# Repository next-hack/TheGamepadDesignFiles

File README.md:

# TheGamepadDesignFiles
 KiCAD design files for The Gamepad, an open source handheld console based on the Arduino Nano Matter Board.

**Notes**
Please use KiCAD 8.0 or later.
Each item in the schematics has its own part number filled so you can easily create the bill of materials.

Building: see https://next-hack.com/index.php/2024/09/21/the-gamepad-an-open-source-diy-handheld-gaming-console

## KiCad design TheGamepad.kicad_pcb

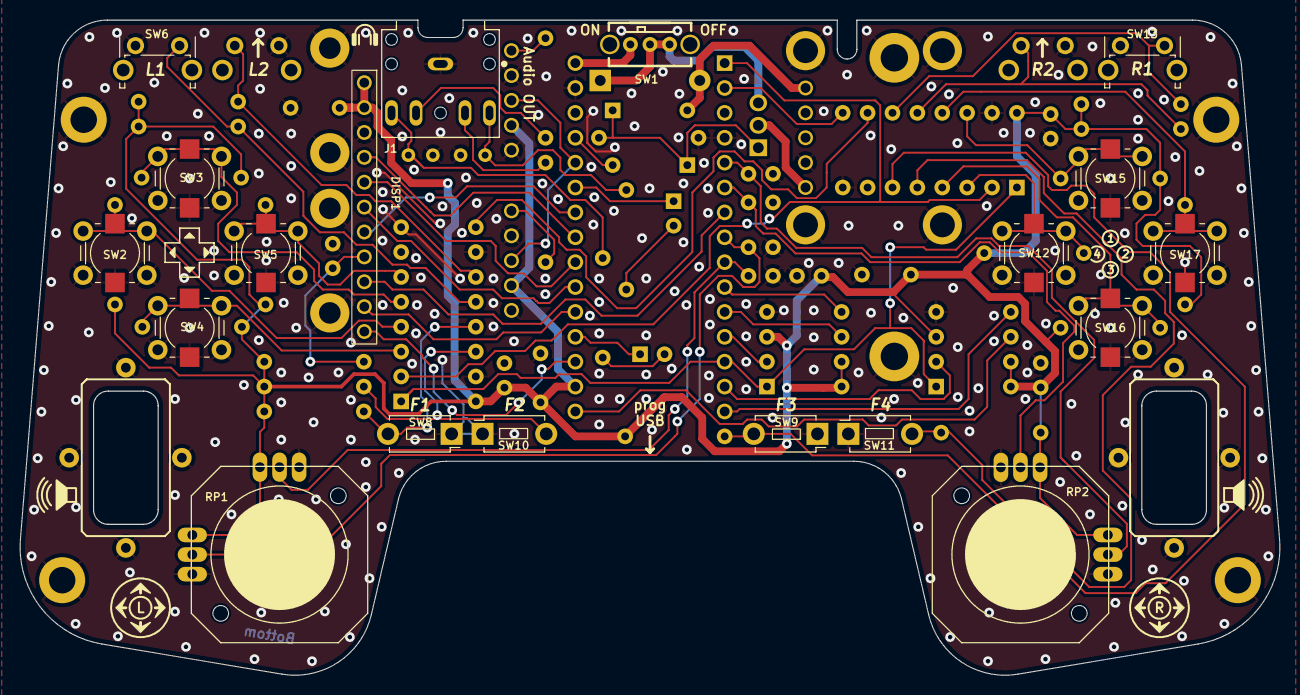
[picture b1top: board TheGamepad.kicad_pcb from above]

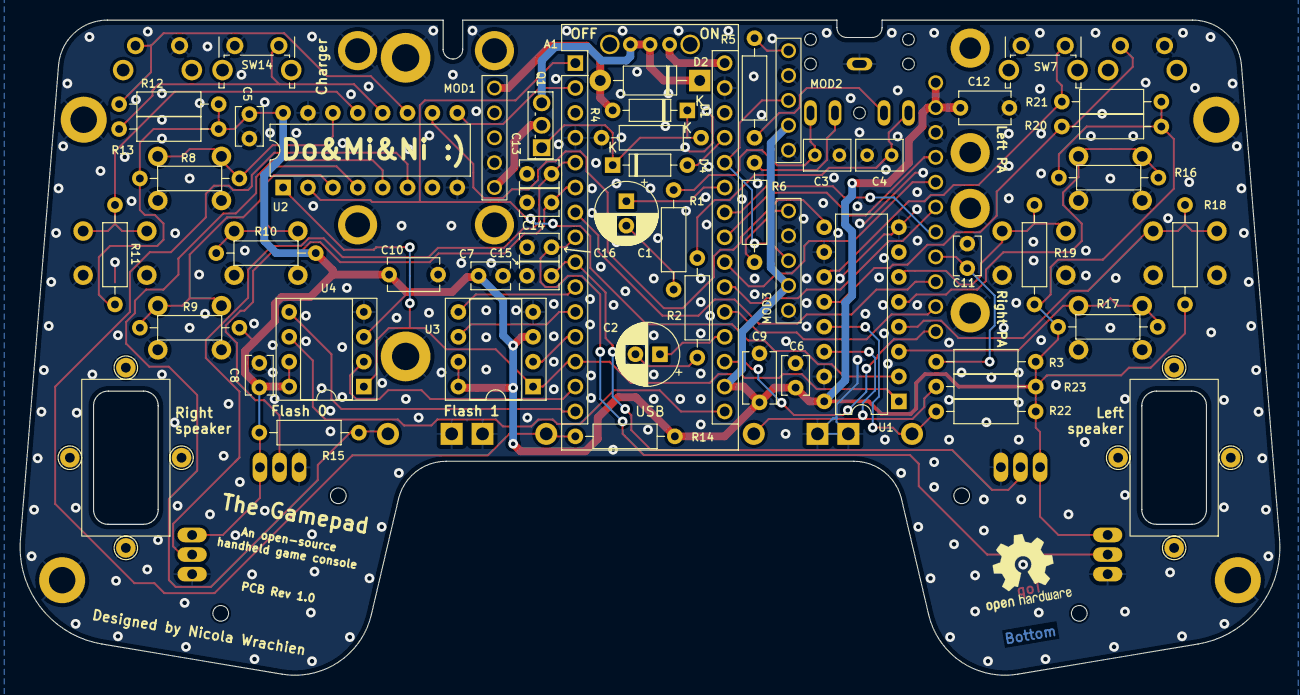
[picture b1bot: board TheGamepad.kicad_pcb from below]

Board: 2 copper layers, 128.6 x 66.9 mm, 86 parts (61 on the bottom side), 57 nets.

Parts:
A1: Arduino_Nano_Matter_swdio_pins; Arduino_Nano_Matter_WithMountingHoles_TP
C1, C2: 100u; CP_Radial_D6.3mm_P2.50mm
C3, C4: 47n; C_Rect_L4.6mm_W3.0mm_P2.50mm_MKS02_FKP02
C5, C6, C7, C8, C11, C13, C14, C15, C16: 100n; C_Disc_D3.8mm_W2.6mm_P2.50mm
C9, C10, C12: 10u; C_Disc_D5.1mm_W3.2mm_P5.00mm
D1, D4: BAT43; D_DO-35_SOD27_P7.62mm_Horizontal
D2: 1N5817; D_DO-41_SOD81_P10.16mm_Horizontal
DISP1: Adafruit4311
H1, H2, H3, H4: V6516F; MountingHole_2.7mm_M2.5_Pad
H43, H44, H45, H46, H47, H48, H49, H50: MountingHole_Pad; TestPoint_THTPad_D2.0mm_Drill1.0mm
J1: SJ1-3525NG; CUI_SJ1-3525NG
LS1, LS2: Speaker; OWS-091630W50A-8
MOD1: ADAFRUIT_4410
MOD2, MOD3: Adafruit-2130
Q1: TSM480P06CH X0G; TO-251-3_Vertical
R1, R2: 330; R_Axial_DIN0207_L6.3mm_D2.5mm_P10.16mm_Horizontal_ExactSilk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
R3, R4, R5, R6, R8, R9, R10, R11, R12, R13, R14, R15, R16, R17, R18, R19, R20, R21, R22, R23: 10k; R_Axial_DIN0207_L6.3mm_D2.5mm_P10.16mm_Horizontal_ExactSilk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
RP1, RP2: Adafruit_2765
SW1: OS102011MA1QN1
SW2, SW3, SW4, SW5, SW12, SW15, SW16, SW17: SW_Push; Adafruit_PB_3983_SW6x6_DUALCASE
SW6, SW7, SW13, SW14: SW_Push; FSMRA2JH04
SW8, SW9, SW10, SW11: SW_Push; PTS636 SL43 LFS
SYM1: Logo_Open_Hardware_Large; OSHW-Logo2_9.8x8mm_SilkScreen
U1, U2: 74HC165; DIP-16_W7.62mm
U3, U4: W25Q64; ADAFRUIT_QSPI8_DIP

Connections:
+3V3: A1.17 (3V3), C5.1, C6.1, C7.1, C8.1, C9.1, C10.1, C12.1, DISP1.10 (3V3), DISP1.11 (VIN), MOD2.4 (VCC), MOD3.4 (VCC), R3.2, R8.2, R9.2, R10.2, R11.2, R12.2, R13.2, R14.2, R15.2, R16.2, R17.2, R18.2, R19.2, R20.2, R21.2, R22.2, R23.2, RP1.X+, RP1.Y+, RP2.X+, RP2.Y+, U1.16 (VCC), U2.16 (VCC), U3.3 (IO2), U3.7 (IO3), U3.8 (VCC), U4.3 (IO2), U4.7 (IO3), U4.8 (VCC)
/A_LEFT: A1.19 (A0/DAC0/PB00), C2.1
/A_RIGHT: A1.25 (A6/DAC1/PB01), C1.1
/BL: A1.18 (AREF/PA00), DISP1.1 (BACKLIGHT)
/DISP_DC: A1.7 (D4/SDA1/PC07), DISP1.3 (D/C)
/DISP_MOSI: A1.21 (A2/PB05), DISP1.6 (MOSI)
/DISP_NCS: A1.24 (A5/SCL/PA07), DISP1.5 (DISP_nCS)
/DISP_SCK: A1.23 (A4/SDA/PA06), DISP1.8 (SCK)
/FLASH_NCS: A1.13 (D10/SS/PTI_SYNC/PD05), U1.1 (~PL), U2.1 (~PL), U3.1 (~CS), U4.1 (~CS)
/K_C0: R22.1, SW8.2, U1.13 (D2)
/K_C1: R23.1, SW10.2, U1.14 (D3)
/K_C2: R14.1, SW9.2, U2.6 (D7)
/K_C3: R15.1, SW11.2, U2.5 (D6)
/K_L_DOWN: R17.1, SW4.2, U1.3 (D4)
/K_L_LEFT: R18.1, SW2.2, U1.4 (D5)
/K_L_RIGHT: R19.1, SW5.2, U1.6 (D7)
/K_L_TDOWN: R21.1, SW7.2, U1.11 (D0)
/K_L_TUP: R20.1, SW6.2, U1.12 (D1)
/K_L_UP: R16.1, SW3.2, U1.5 (D6)
/K_R_DOWN: R9.1, SW16.2, U2.4 (D5)
/K_R_LEFT: R10.1, SW12.2, U2.3 (D4)
/K_R_RIGHT: R11.1, SW17.2, U2.13 (D2)
/K_R_TDOWN: R13.1, SW14.2, U2.12 (D1)
/K_R_TUP: R12.1, SW13.2, U2.11 (D0)
/K_R_UP: R8.1, SW15.2, U2.14 (D3)
/MISO_0: A1.14 (D11/MOSI/PA09), U4.2 (DO(IO1))
/MISO_1: A1.12 (D9/PTI_DATA/PD04), U3.2 (DO(IO1))
/MOSI_0: A1.15 (D12/MISO/PA08), U4.5 (DI(IO0))
/MOSI_1: A1.10 (D7/PD02), U3.5 (DI(IO0))
/POT0X: A1.8 (D5/SCL1/PC08), C16.1, RP1.X
/POT0Y: A1.9 (D6/PC09), C15.1, RP1.Y
/POT1X: A1.6 (D3/SS1/PC06), C14.1, RP2.X
/POT1Y: A1.5 (D2/SCK1/SWV/PA03), C13.1, RP2.Y
/SCK_0: A1.16 (D13/SCK/PB04), U4.6 (CLK)
/SCK_1: A1.11 (D8/PD03), U3.6 (CLK)
/SD_MISO: A1.22 (A3/PC00), DISP1.7 (MISO)
/SD_NCS: A1.20 (A1/DAC2/PB02), DISP1.2 (SD_nCS)
/SR_CK: A1.1 (D0/MOSI1/TX/PA04), U1.2 (CP), U2.2 (CP)
/SR_D: A1.2 (D1/RX/MISO1/PA05), U2.9 (Q7)
/~AUDIO_SD: A1.26 (A7/DAC3/PB03), MOD2.3 (~SD), MOD3.3 (~SD)
GND: A1.4 (GND), A1.29 (GND), C3.2, C4.2, C5.2, C6.2, C7.2, C8.2, C9.2, C10.2, C11.2, C12.2, C13.2, C14.2, C15.2, C16.2, DISP1.9 (GND), DISP1.12 (S1), DISP1.13 (S2), H1.1, H2.1, H3.1, H4.1, H43.1, H44.1, H45.1, H46.1, H47.1, H48.1, H49.1, H50.1, J1.1, MOD1.4 (GND), MOD1.6 (HOLDER), MOD2.2 (IN-), MOD2.5 (GND), MOD2.8 (H), MOD2.9 (H), MOD3.2 (IN-), MOD3.5 (GND), MOD3.8 (H), MOD3.9 (H), R4.2, RP1.X-, RP1.Y-, RP2.X-, RP2.Y-, SW2.1, SW3.1, SW4.1, SW5.1, SW6.1, SW7.1, SW8.1, SW9.1, SW10.1, SW11.1, SW12.1, SW13.1, SW14.1, SW15.1, SW16.1, SW17.1, U1.8 (GND), U1.10 (DS), U1.15 (~CE), U2.8 (GND), U2.15 (~CE), U3.4 (GND), U4.4 (GND)
unnamed: A1.27 (+5V), D4.2 (A)
unnamed: A1.30 (VIN), SW1.1 (A)
unnamed: C1.2, R1.1
unnamed: C2.2, R2.1
unnamed: C3.1, J1.3, R1.2
unnamed: C4.1, J1.2, R2.2
unnamed: D1.2 (A), D2.2 (A), MOD1.1 (5V)
unnamed: D1.1 (K), D4.1 (K), Q1.1 (G), R4.1
unnamed: D2.1 (K), Q1.3 (S), SW1.2 (B), SW1.3 (C)
unnamed: C11.1, DISP1.4 (nRESET), R3.1
unnamed: J1.4, R5.2
unnamed: J1.5, R6.2
unnamed: MOD1.5 (VBAT), Q1.2 (D)
unnamed: MOD2.1 (IN+), R5.1
unnamed: MOD3.1 (IN+), R6.1
unnamed: U1.9 (Q7), U2.10 (DS)

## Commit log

2024-10-01 Initial commit.
